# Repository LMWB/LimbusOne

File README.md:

# LimbusOne
Custom Microcontroller Board based on STM32F042-Series

[schematics](/Hardware/LimbusOne/PDF/LimbusOne.pdf)

 Features
- STM32F042K6T6 Microcontroller
- it got a crystal oscillator but I did not use it
    - accuracy is good since USB Data is working
- Power indicator LED
- User LED
- User Push Button
- Industrial ready CAN-Bus interface
    - works with standard (11-Bit) and extended (29-Bit) CAN identifier
- Industrial ready Modbus interface
- USB mini as power supply AND DATA
    - unfortunately USB and CAN share same Pin's so the user has to decide what to use
- 2.54mm Pin Headers for debugging and tracing
- debug / programming interface according to STLink that comes with most of STM32 Nucleo Boards

# Todo
- adjust Pin Header spacing to a more usable spacing, right know its pretty random

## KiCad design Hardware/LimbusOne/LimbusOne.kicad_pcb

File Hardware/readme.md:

here you can find the KiCad EDA project files

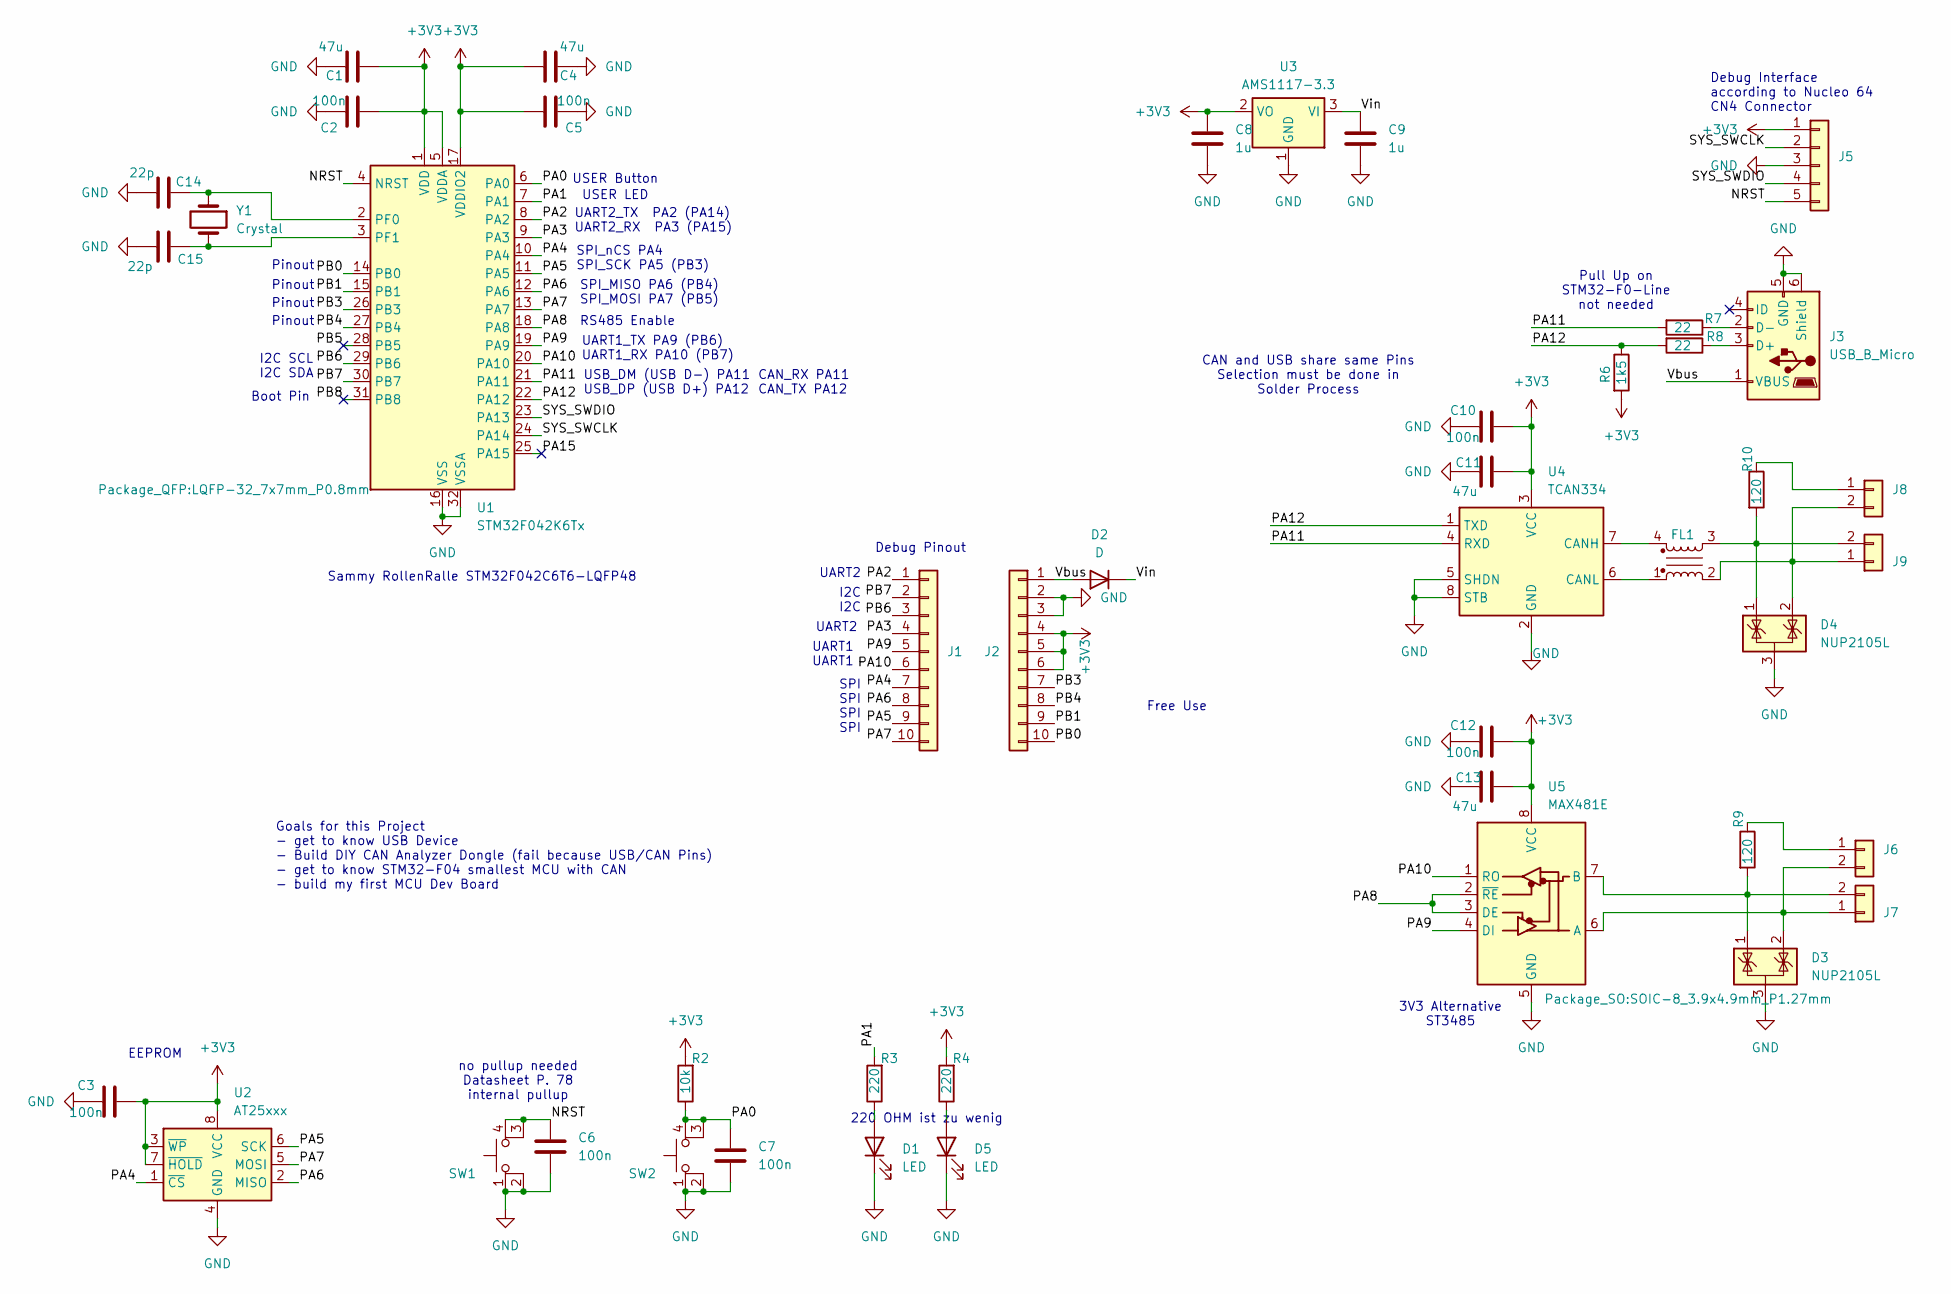
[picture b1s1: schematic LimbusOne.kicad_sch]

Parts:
C1, C4, C11, C13: 47u; C_1206_3216Metric
C2, C3, C5, C6, C7, C10, C12: 100n; C_1206_3216Metric
C8, C9: 1u; C_1206_3216Metric
C14, C15: 22p; C_1206_3216Metric
D1, D5: LED; LED_1206_3216Metric
D2: D; D_1206_3216Metric
D3, D4: NUP2105L; SOT-23
FL1: Filter_CAN_Choke_LL_1234; WE-CNSW_1812
J1, J2: Conn_01x10; PinHeader_1x10_P2.54mm_Vertical
J3: USB_B_Micro; USB_Mini-B_Lumberg_2486_01_Horizontal
J5: Conn_01x05; PinHeader_1x05_P2.54mm_Horizontal
J6, J8: Conn_01x02; PinHeader_1x02_P2.54mm_Vertical
J7, J9: Conn_01x02; TerminalBlock_Phoenix_MPT-0,5-2-2.54_1x02_P2.54mm_Horizontal
R2: 10k; R_1206_3216Metric
R3, R4: 220; R_1206_3216Metric
R6: 1k5; R_1206_3216Metric
R7, R8: 22; R_1206_3216Metric
R9, R10: 120; R_1206_3216Metric
SW1, SW2: SW_MEC_5E; 430181038816
U1: STM32F042K6Tx; LQFP-32_7x7mm_P0.8mm
U2: AT25xxx; SOIC-8_3.9x4.9mm_P1.27mm
U3: AMS1117-3.3; SOT-223-3_TabPin2
U4: TCAN334; SOIC-8_3.9x4.9mm_P1.27mm
U5: MAX481E; SOIC-8_3.9x4.9mm_P1.27mm
Y1: Crystal; Crystal_SMD_HC49-SD

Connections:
+3V3: C1.2, C2.2, C3.2, C4.2, C5.2, C8.1, C10.2, C11.2, C12.2, C13.2, J2.4, J2.5, J2.6, J5.1, R2.2, R4.2, R6.2, U1.1 (VDD), U1.5 (VDDA), U1.17 (VDDIO2), U2.3 (~WP), U2.7 (~HOLD), U2.8 (VCC), U3.2 (VO), U4.3 (VCC), U5.8 (VCC)
/NRST: C6.1, J5.5, SW1.3 (K), SW1.4 (A), U1.4 (NRST)
/PA0: C7.1, R2.1, SW2.3 (K), SW2.4 (A), U1.6 (PA0)
/PA1: R3.2, U1.7 (PA1)
/PA2: J1.1, U1.8 (PA2)
/PA3: J1.4, U1.9 (PA3)
/PA4: J1.7, U1.10 (PA4), U2.1 (~CS)
/PA5: J1.9, U1.11 (PA5), U2.6 (SCK)
/PA6: J1.8, U1.12 (PA6), U2.2 (MISO)
/PA7: J1.10, U1.13 (PA7), U2.5 (MOSI)
/PA8: U1.18 (PA8), U5.2 (~RE), U5.3 (DE)
/PA9: J1.5, U1.19 (PA9), U5.4 (DI)
/PA10: J1.6, U1.20 (PA10), U5.1 (RO)
/PA11: R7.2, U1.21 (PA11), U4.4 (RXD)
/PA12: R6.1, R8.2, U1.22 (PA12), U4.1 (TXD)
/PA15: U1.25 (PA15)
/PB0: J2.10, U1.14 (PB0)
/PB1: J2.9, U1.15 (PB1)
/PB3: J2.7, U1.26 (PB3)
/PB4: J2.8, U1.27 (PB4)
/PB5: U1.28 (PB5)
/PB6: J1.3, U1.29 (PB6)
/PB7: J1.2, U1.30 (PB7)
/PB8: U1.31 (PB8)
/SYS_SWCLK: J5.2, U1.24 (PA14)
/SYS_SWDIO: J5.4, U1.23 (PA13)
/Vbus: D2.2 (A), J2.1, J3.1 (VBUS)
/Vin: C9.1, D2.1 (K), U3.3 (VI)
GND: C1.1, C2.1, C3.1, C4.1, C5.1, C6.2, C7.2, C8.2, C9.2, C10.1, C11.1, C12.1, C13.1, C14.1, C15.1, D1.1 (K), D3.3 (A), D4.3 (A), D5.1 (K), J2.2, J2.3, J3.5 (GND), J3.6 (Shield), J5.3, SW1.1, SW1.2, SW2.1, SW2.2, U1.16 (VSS), U1.32 (VSSA), U2.4 (GND), U3.1 (GND), U4.2 (GND), U4.5 (SHDN), U4.8 (STB), U5.5 (GND)
unnamed: D1.2 (A), R3.1
unnamed: D5.2 (A), R4.1
unnamed: J3.3 (D+), R8.1
unnamed: J3.2 (D-), R7.1
unnamed: J6.1, R9.1
unnamed: D3.2 (K), J6.2, J7.1, U5.6 (A)
unnamed: D3.1 (K), J7.2, R9.2, U5.7 (B)
unnamed: J8.1, R10.1
unnamed: D4.2 (K), FL1.2, J8.2, J9.1
unnamed: D4.1 (K), FL1.3, J9.2, R10.2
unnamed: C14.2, U1.2 (PF0), Y1.1
unnamed: C15.2, U1.3 (PF1), Y1.2
unnamed: FL1.4, U4.7 (CANH)
unnamed: FL1.1, U4.6 (CANL)

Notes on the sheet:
RS485 Enable
Goals for this Project - get to know USB Device - Build DIY CAN Analyzer Dongle (fail because USB/CAN Pins) - get to know STM32-F04 smallest MCU with CAN - build my first MCU Dev Board
Free Use
SPI SPI SPI SPI
Pinout
USB_DM (USB D-) PA11 USB_DP (USB D+) PA12
Sammy RollenRalle STM32F042C6T6-LQFP48
USER LED
USER Button
3V3 Alternative ST3485
I2C I2C
Boot Pin
I2C SCL I2C SDA
Debug Pinout
UART1 UART1
UART1_TX PA9 (PB6) UART1_RX PA10 (PB7)
SPI_MISO PA6 (PB4) SPI_MOSI PA7 (PB5)
UART2_TX PA2 (PA14) UART2_RX PA3 (PA15)
UART2
220 OHM ist zu wenig
EEPROM
CAN and USB share same Pins Selection must be done in Solder Process
CAN_RX PA11 CAN_TX PA12
Debug Interface according to Nucleo 64 CN4 Connector
no pullup needed Datasheet P. 78 internal pullup
Pull Up on STM32-F0-Line not needed
SPI_nCS PA4 SPI_SCK PA5 (PB3)

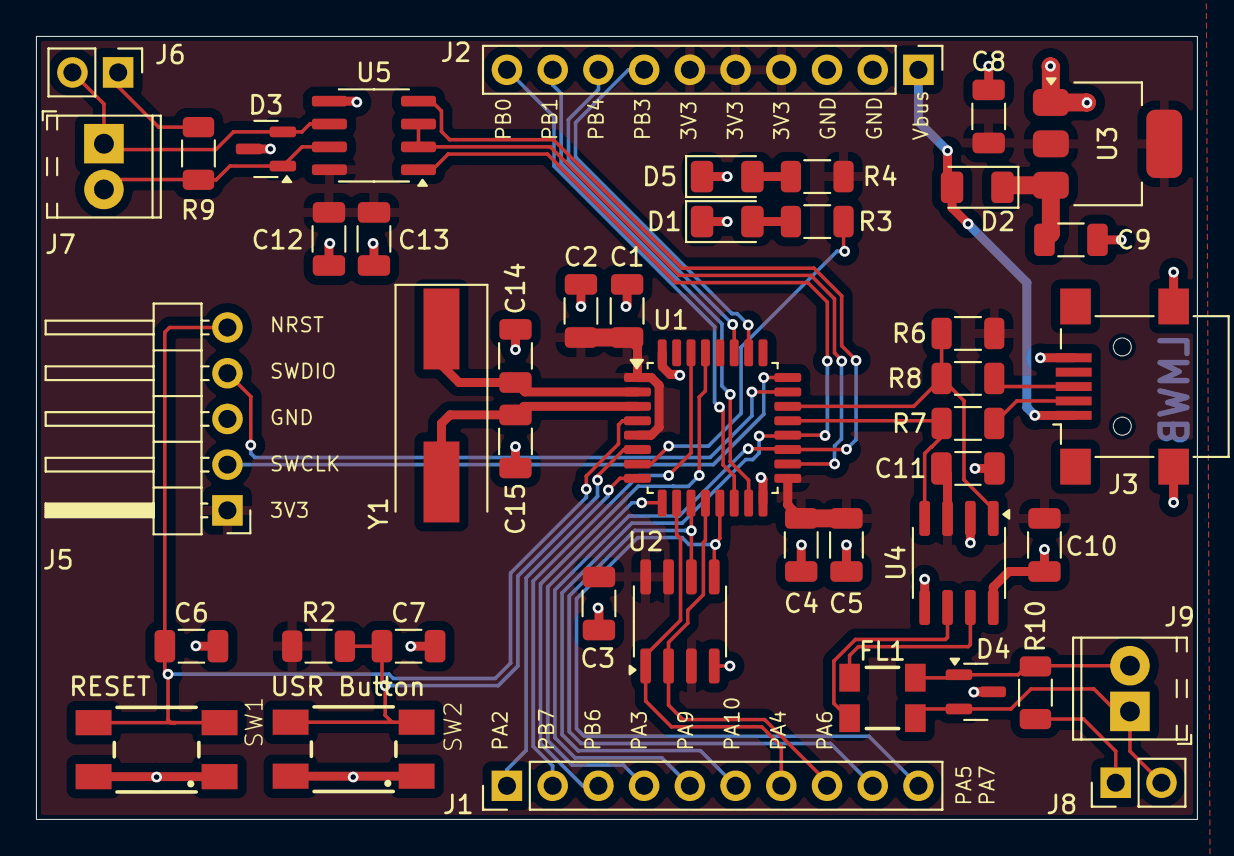
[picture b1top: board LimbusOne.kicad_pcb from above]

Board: 2 copper layers, 64.5 x 43.5 mm, 45 parts (0 on the bottom side), 40 nets.

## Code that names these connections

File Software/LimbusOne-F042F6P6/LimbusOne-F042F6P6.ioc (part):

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Mcu.Name=STM32F042F6Px
Mcu.Package=TSSOP20
Mcu.UserName=STM32F042F6Px
PA11.Mode=Device
PA11.Signal=USB_DM
PA12.Mode=Device
PA12.Signal=USB_DP
PA13.Mode=Serial_Wire
PA13.Signal=SYS_SWDIO
PA14.Mode=Serial_Wire
PA14.Signal=SYS_SWCLK
PA2.Mode=Asynchronous
PA2.Signal=USART2_TX
PA3.Mode=Asynchronous
PA3.Signal=USART2_RX
PA5.Mode=Full_Duplex_Master
PA5.Signal=SPI1_SCK
PA6.Mode=Full_Duplex_Master
PA6.Signal=SPI1_MISO
PA7.Mode=Full_Duplex_Master
PA7.Signal=SPI1_MOSI
PB1.GPIOParameters=GPIO_Label
PB1.GPIO_Label=LED3
PB1.Signal=GPIO_Output
PB8.Mode=I2C
PB8.Signal=I2C1_SCL
PF0-OSC_IN.Mode=I2C
PF0-OSC_IN.Signal=I2C1_SDA
RCC.SYSCLKFreq_VALUE=48000000
RCC.SYSCLKSource=RCC_SYSCLKSOURCE_HSI48
board=custom

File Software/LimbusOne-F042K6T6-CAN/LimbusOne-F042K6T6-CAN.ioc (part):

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Mcu.Name=STM32F042K(4-6)Tx
Mcu.Package=LQFP32
Mcu.UserName=STM32F042K6Tx
PA1.GPIOParameters=GPIO_Label
PA1.GPIO_Label=LED1
PA1.Signal=GPIO_Output
PA10.Mode=Asynchronous
PA10.Signal=USART1_RX
PA11.GPIOParameters=GPIO_PuPd
PA11.GPIO_PuPd=GPIO_NOPULL
PA11.Mode=CAN_Activate
PA11.Signal=CAN_RX
PA12.GPIOParameters=GPIO_PuPd
PA12.GPIO_PuPd=GPIO_NOPULL
PA12.Mode=CAN_Activate
PA12.Signal=CAN_TX
PA13.Mode=Serial_Wire
PA13.Signal=SYS_SWDIO
PA14.Mode=Serial_Wire
PA14.Signal=SYS_SWCLK
PA2.Mode=Asynchronous
PA2.Signal=USART2_TX
PA3.Mode=Asynchronous
PA3.Signal=USART2_RX
PA9.Mode=Asynchronous
PA9.Signal=USART1_TX
RCC.SYSCLKFreq_VALUE=48000000
RCC.SYSCLKSource=RCC_SYSCLKSOURCE_HSI48
board=custom

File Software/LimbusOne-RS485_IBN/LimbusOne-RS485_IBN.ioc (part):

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Mcu.Name=STM32F042K(4-6)Tx
Mcu.Package=LQFP32
Mcu.UserName=STM32F042K6Tx
PA0.GPIOParameters=GPIO_Label
PA0.GPIO_Label=B1
PA0.Signal=GPXTI0
PA1.GPIOParameters=GPIO_Label
PA1.GPIO_Label=LED1
PA1.Signal=GPIO_Output
PA10.Mode=Asynchronous
PA10.Signal=USART1_RX
PA13.Mode=Serial_Wire
PA13.Signal=SYS_SWDIO
PA14.Mode=Serial_Wire
PA14.Signal=SYS_SWCLK
PA8.GPIOParameters=GPIO_Label
PA8.GPIO_Label=RS485_nREDE
PA8.Signal=GPIO_Output
PA9.Mode=Asynchronous
PA9.Signal=USART1_TX
RCC.SYSCLKFreq_VALUE=48000000
RCC.SYSCLKSource=RCC_SYSCLKSOURCE_HSI48
board=custom

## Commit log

2024-07-16 added images and pimp readme
2024-07-16 pimp readme
2024-11-21 added hardware files, updated gitignore
2024-11-21 added hardware/readme.md
2024-11-21 added software files
